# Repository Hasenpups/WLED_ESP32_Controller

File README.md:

Shield: [![CC BY-NC-SA 4.0][cc-by-nc-sa-shield]][cc-by-nc-sa]

This work is licensed under a
[Creative Commons Attribution-NonCommercial-ShareAlike 4.0 International License][cc-by-nc-sa].

[![CC BY-NC-SA 4.0][cc-by-nc-sa-image]][cc-by-nc-sa]

[cc-by-nc-sa]: http://creativecommons.org/licenses/by-nc-sa/4.0/
[cc-by-nc-sa-image]: https://licensebuttons.net/l/by-nc-sa/4.0/88x31.png
[cc-by-nc-sa-shield]: https://img.shields.io/badge/License-CC%20BY--NC--SA%204.0-lightgrey.svg

## Donations / Spenden
If somebody wants to support me for upcoming projects :)  
- PayPal:  
- Amazon Giftcard: https://www.amazon.de/Amazon-Gutschein-per-E-Mail-Amazon/dp/B0054PDOV8 - stefan.riese@me.com

# WLED ESP32 Controller
This board is designed to connect addressable LEDs/Neopixel strips and handle them with the WLED firmware. Other firmware can be used as well.

## Features
- 5V/GND connector for input voltage
- 4 output lines for LED data or relais
- level shifter for all 4 outputs (3.3V -> 5V )
- resistor for data lines
- support for LED strips with clock signal
- connector for microphone sensor or button input (ADC1, GND, 3.3V, IN1, GND, IN2, GND)
- connector to flash firmware with CP2104 (3.3V, TX, RX, GND)

## BOM
- 1 x WLED ESP32 Controller presoldered from https://jlcpcb.com/

|Comment|Designator|Footprint|LCSC
|---|---|---|---
10µ|C1,C3|Capacitor_SMD:C_0805_2012Metric_Pad1.18x1.45mm_HandSolder|C15850
47µ|C2|Capacitor_SMD:C_0805_2012Metric_Pad1.18x1.45mm_HandSolder|C16780
100n|C4,C5|Capacitor_SMD:C_0805_2012Metric_Pad1.18x1.45mm_HandSolder|C49678
MountingHole|H1,H2|MountingHole:MountingHole_3.2mm_M3_DIN965|
Conn_01x06_Female|J1|TerminalBlock:TerminalBlock_bornier-6_P5.08mm|
Conn_01x04_Female|J2|Connector_PinHeader_2.54mm:PinHeader_1x04_P2.54mm_Vertical|
Conn_01x07_Female|J3|Connector_PinHeader_2.54mm:PinHeader_1x07_P2.54mm_Vertical|
Jumper_NO_Small|JP1,JP2,JP3,JP4|Jumper:SolderJumper-2_P1.3mm_Open_RoundedPad1.0x1.5mm|
330|R1,R2,R3,R4|Resistor_SMD:R_0805_2012Metric_Pad1.20x1.40mm_HandSolder|C17630
10K|R5,R6|Resistor_SMD:R_0805_2012Metric_Pad1.20x1.40mm_HandSolder|C17414
Reset|SW1|Button_Switch_SMD:SW_SPST_CK_RS282G05A3|C354943
Flash|SW2|Button_Switch_SMD:SW_SPST_CK_RS282G05A3|C354943
AMS1117-3.3|U1|Package_TO_SOT_SMD:SOT-223-3_TabPin2|C6186
ESP32-WROOM-32|U2|RF_Module:ESP32-WROOM-32|C82899
SN74AHCT125D|U3|WLED_ESP32:SOIC127P600X175-14N|C155176

- 3 x 2-pin screw terminal (https://www.amazon.de/gp/product/B08JB6SSCJ)
- 1 x 4-pin header male
- 1 x 7-pin header male

## Wiring diagram
- https://github.com/Hasenpups/WLED_ESP32_Controller/blob/main/WLED_ESP32_Controller.pdf

## Software
- WLED: https://github.com/Aircoookie/WLED/releases
- Sound Reactive WLED: https://github.com/atuline/WLED/releases

## How to flash software
- Connect USB-UART bridge to 3.3V, TX, RX and GND
    - https://de.aliexpress.com/item/1005002689033373.html
    - https://www.makershop.de/module/kommunikation-module/micro-usb-uart-ttl/
- Press and hold "Flash" button
- Press "Reset" button and release
- Release "Flash" button
- Open https://install.wled.me/
- Click "Install"
- Select COM port of USB-UART bridge
- Wait until finished

## WLED configuration
- OUT1 - IO16
- OUT2 - IO17
- OUT3 - IO18
- OUT4 - IO19
- Microphone input - IO36
- Button input 1 - IO26
- Button input 2 - IO27

## Case
- https://www.prusaprinters.org/prints/124223-wled-controller-base-housing
- https://www.printables.com/model/163438-housing-for-esp32-wled-controller

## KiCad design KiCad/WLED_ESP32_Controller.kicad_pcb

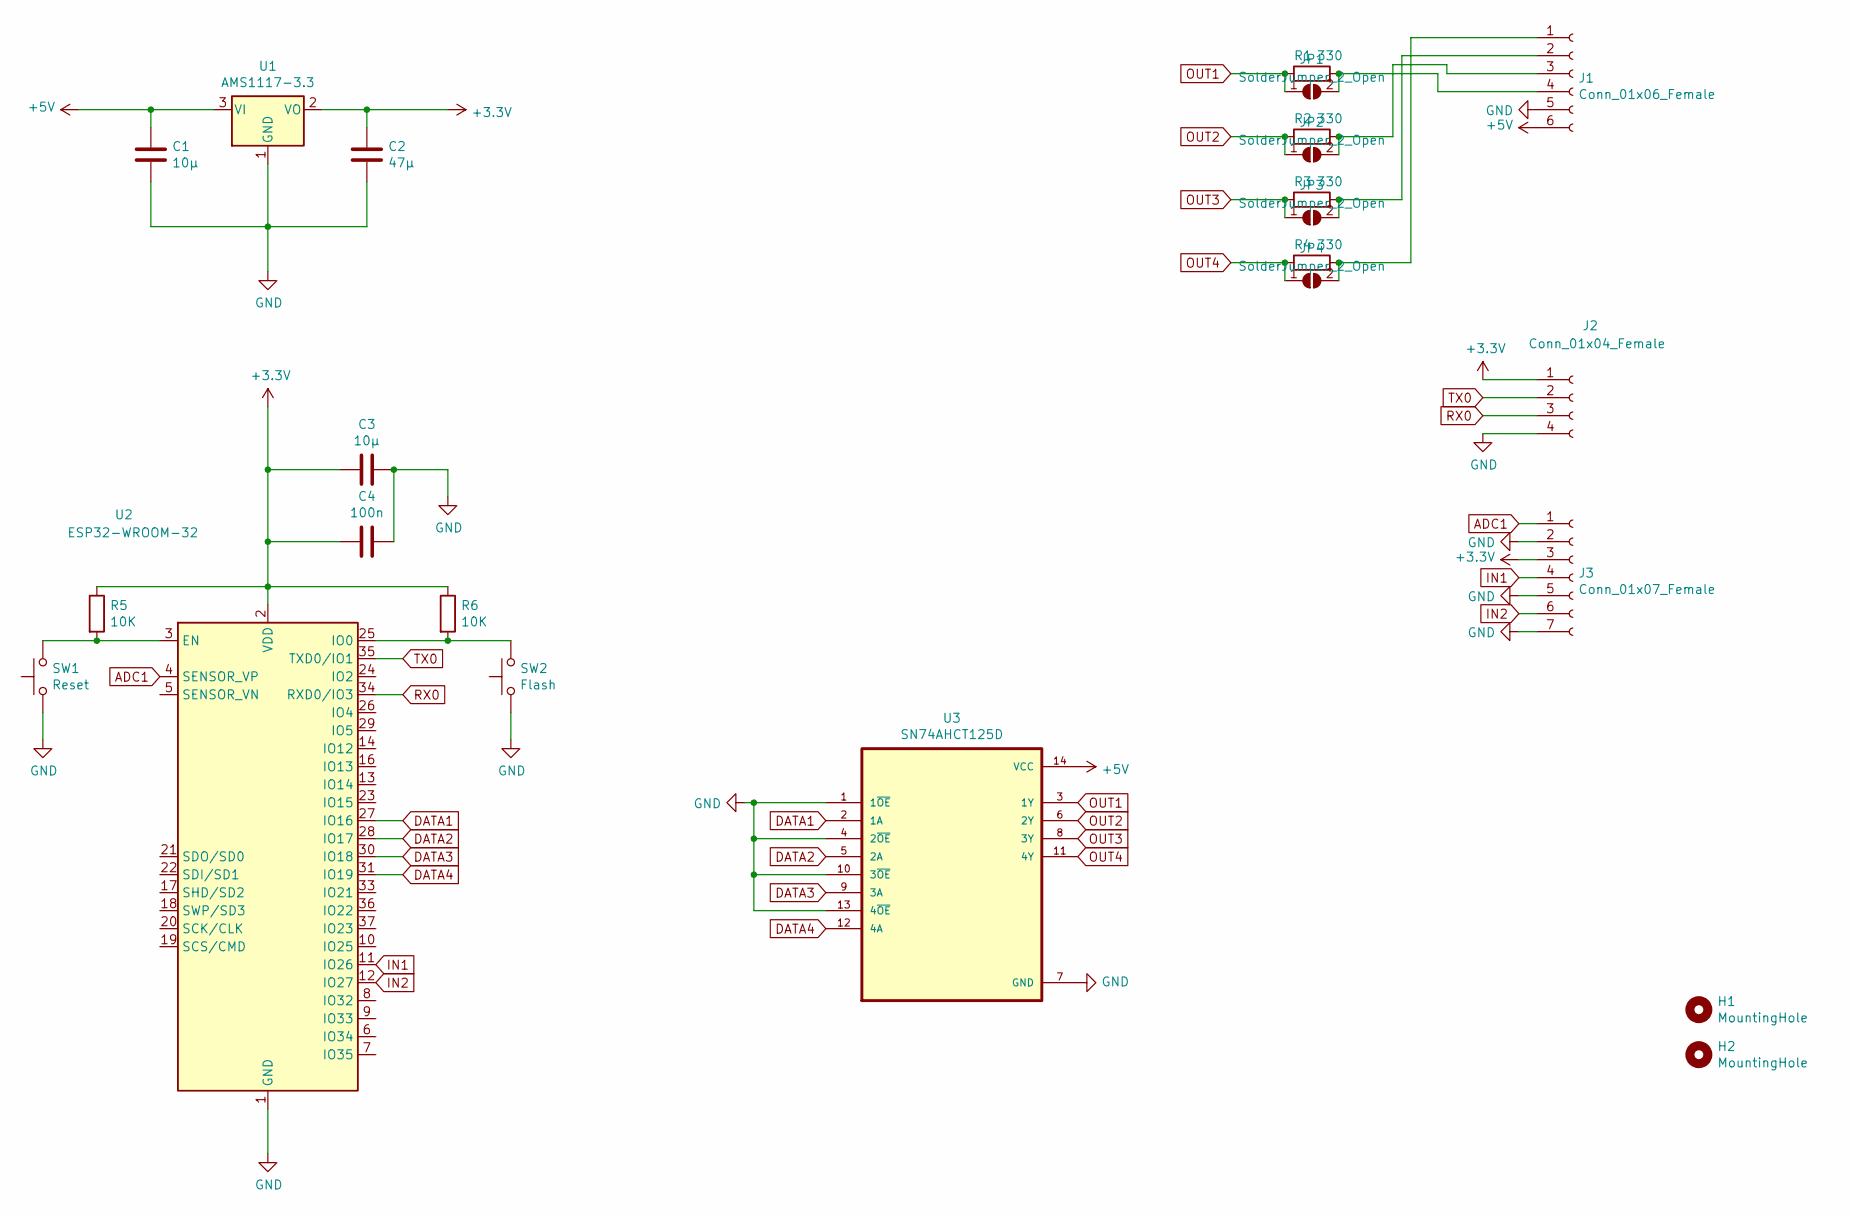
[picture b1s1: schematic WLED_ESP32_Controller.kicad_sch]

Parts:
C1, C3: 10µ; C_0805_2012Metric_Pad1.18x1.45mm_HandSolder
C2: 47µ; C_0805_2012Metric_Pad1.18x1.45mm_HandSolder
C4: 100n; C_0805_2012Metric_Pad1.18x1.45mm_HandSolder
H1, H2: MountingHole; MountingHole_3.2mm_M3_DIN965
J1: Conn_01x06_Female; TerminalBlock_bornier-6_P5.08mm
J2: Conn_01x04_Female; PinHeader_1x04_P2.54mm_Vertical
J3: Conn_01x07_Female; PinHeader_1x07_P2.54mm_Vertical
JP1, JP2, JP3, JP4: SolderJumper_2_Open; SolderJumper-2_P1.3mm_Open_Pad1.0x1.5mm
R1, R2, R3, R4: 330; R_0805_2012Metric_Pad1.20x1.40mm_HandSolder
R5, R6: 10K; R_0805_2012Metric_Pad1.20x1.40mm_HandSolder
SW1: Reset; SW_SPST_CK_RS282G05A3
SW2: Flash; SW_SPST_CK_RS282G05A3
U1: AMS1117-3.3; SOT-223-3_TabPin2
U2: ESP32-WROOM-32
U3: SN74AHCT125D; SOIC127P600X175-14N

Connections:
+3.3V: C2.1, C3.2, C4.2, J2.1, J3.3, R5.1, R6.1, U1.2 (VO), U2.2 (VDD)
+5V: C1.1, J1.6, U1.3 (VI), U3.14 (VCC)
ADC1: J3.1, U2.4 (SENSOR_VP)
DATA1: U2.27 (IO16), U3.2 (1A)
DATA2: U2.28 (IO17), U3.5 (2A)
DATA3: U2.30 (IO18), U3.9 (3A)
DATA4: U2.31 (IO19), U3.12 (4A)
GND: C1.2, C2.2, C3.1, C4.1, J1.5, J2.4, J3.2, J3.5, J3.7, SW1.1, SW2.1, U1.1 (GND), U2.1 (GND), U2.15 (GND), U2.38 (GND), U2.39 (GND), U3.1 (1~OE), U3.4 (2~OE), U3.7 (GND), U3.10 (3~OE), U3.13 (4~OE)
IN1: J3.4, U2.11 (IO26)
IN2: J3.6, U2.12 (IO27)
unnamed: J1.1, JP4.2 (B), R4.2
unnamed: J1.2, JP3.2 (B), R3.2
unnamed: J1.3, JP2.2 (B), R2.2
unnamed: J1.4, JP1.2 (B), R1.2
unnamed: R5.2, SW1.2, U2.3 (EN)
unnamed: R6.2, SW2.2, U2.25 (IO0)
OUT1: JP1.1 (A), R1.1, U3.3 (1Y)
OUT2: JP2.1 (A), R2.1, U3.6 (2Y)
OUT3: JP3.1 (A), R3.1, U3.8 (3Y)
OUT4: JP4.1 (A), R4.1, U3.11 (4Y)
RX0: J2.3, U2.34 (RXD0/IO3)
TX0: J2.2, U2.35 (TXD0/IO1)

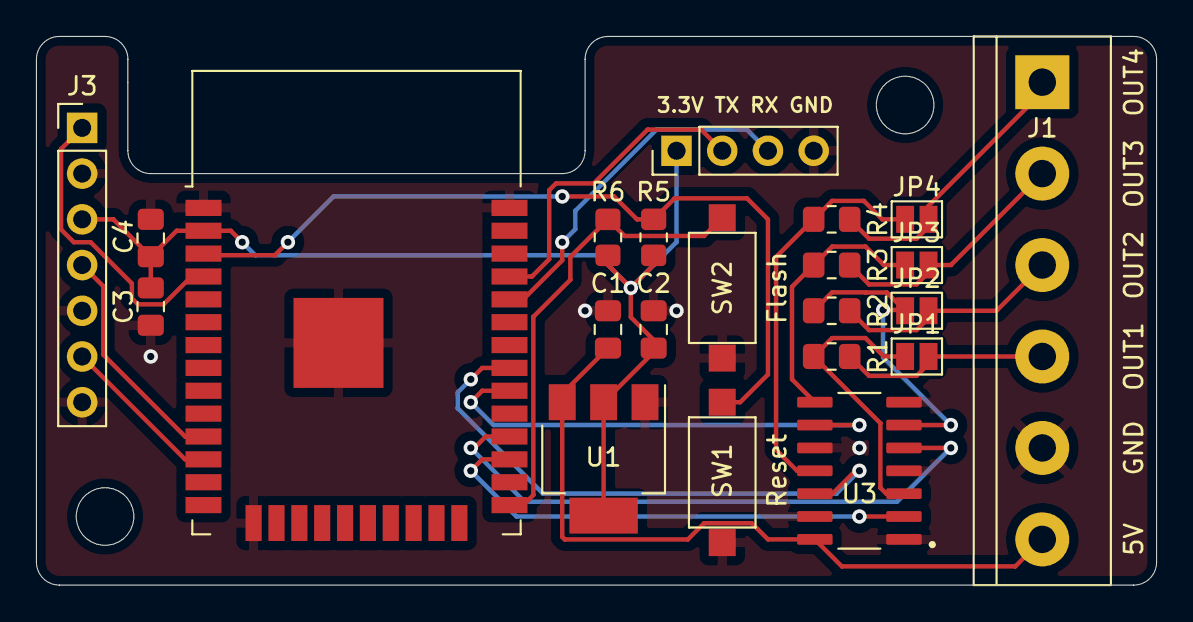
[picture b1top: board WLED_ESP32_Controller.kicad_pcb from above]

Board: 2 copper layers, 62.2 x 30.5 mm, 24 parts (0 on the bottom side), 22 nets.

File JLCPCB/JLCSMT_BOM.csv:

Comment,Designator,Footprint,LCSC
"10µ","C1,C3","Capacitor_SMD:C_0805_2012Metric_Pad1.18x1.45mm_HandSolder","C15850"
"47µ","C2","Capacitor_SMD:C_0805_2012Metric_Pad1.18x1.45mm_HandSolder","C16780"
"100n","C4,C5","Capacitor_SMD:C_0805_2012Metric_Pad1.18x1.45mm_HandSolder","C49678"
"MountingHole","H1,H2","MountingHole:MountingHole_3.2mm_M3_DIN965",""
"Conn_01x06_Female","J1","TerminalBlock:TerminalBlock_bornier-6_P5.08mm",""
"Conn_01x04_Female","J2","Connector_PinHeader_2.54mm:PinHeader_1x04_P2.54mm_Vertical",""
"Conn_01x07_Female","J3","Connector_PinHeader_2.54mm:PinHeader_1x07_P2.54mm_Vertical",""
"Jumper_NO_Small","JP1,JP2,JP3,JP4","Jumper:SolderJumper-2_P1.3mm_Open_RoundedPad1.0x1.5mm",""
"330","R1,R2,R3,R4","Resistor_SMD:R_0805_2012Metric_Pad1.20x1.40mm_HandSolder","C17630"
"10K","R5,R6","Resistor_SMD:R_0805_2012Metric_Pad1.20x1.40mm_HandSolder","C17414"
"Reset","SW1","Button_Switch_SMD:SW_SPST_CK_RS282G05A3","C354943"
"Flash","SW2","Button_Switch_SMD:SW_SPST_CK_RS282G05A3","C354943"
"AMS1117-3.3","U1","Package_TO_SOT_SMD:SOT-223-3_TabPin2","C6186"
"ESP32-WROOM-32","U2","RF_Module:ESP32-WROOM-32","C82899"
"SN74AHCT125D","U3","WLED_ESP32:SOIC127P600X175-14N","C155176"

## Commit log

2022-06-21 reupload
2022-06-21 - reupload
2023-01-18 - add KiCad files
2023-01-18 - update URL
